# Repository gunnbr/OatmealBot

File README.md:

# OatmealBot
OatmealBot is a robot built on a circular platform using 3 [omni wheels](https://en.wikipedia.org/wiki/Omni_wheel) and
controlled using a PS3 controller. It's named OatmealBot because it was
originally designed so the control hardware could be hidden under a
cylindrical box of oatmeal.

## Features
This OatmealBot controller is built on top of the
[Adafruit Motor Hat](http://adafru.it/2348). This board provides the
following features on top of that:
* Powers the Hat and the Pi from a [Pololu 5V regulator](https://www.pololu.com/product/2858)
* Plug for 4
[Pololu motors with quadrature encoder](https://www.pololu.com/product/3240)
* Plugs for 3 servos
* 2 high power outputs
* Plug for [SPI OLED display](http://adafru.ti/938)
* 2 LED (status & error)
* Plug for
[FTDI TTL serial to USB adapter](http://www.ftdichip.com/Support/Documents/DataSheets/Cables/DS_TTL-232R_CABLES.pdf)

## History
This was initially envisioned using a SAMD21 controller so the motor
encoders could be read by hardware counters. However, I couldn't find
a good Bluetooth driver that worked. Although I found some existing
drivers that could be ported, I realized I could just as well get
a Raspberry Pi Zero W with built-in Bluetooth and a motor hat and
see how well it works without reading the encoders. Turns out it
worked fairly well, so I kept working down this path.

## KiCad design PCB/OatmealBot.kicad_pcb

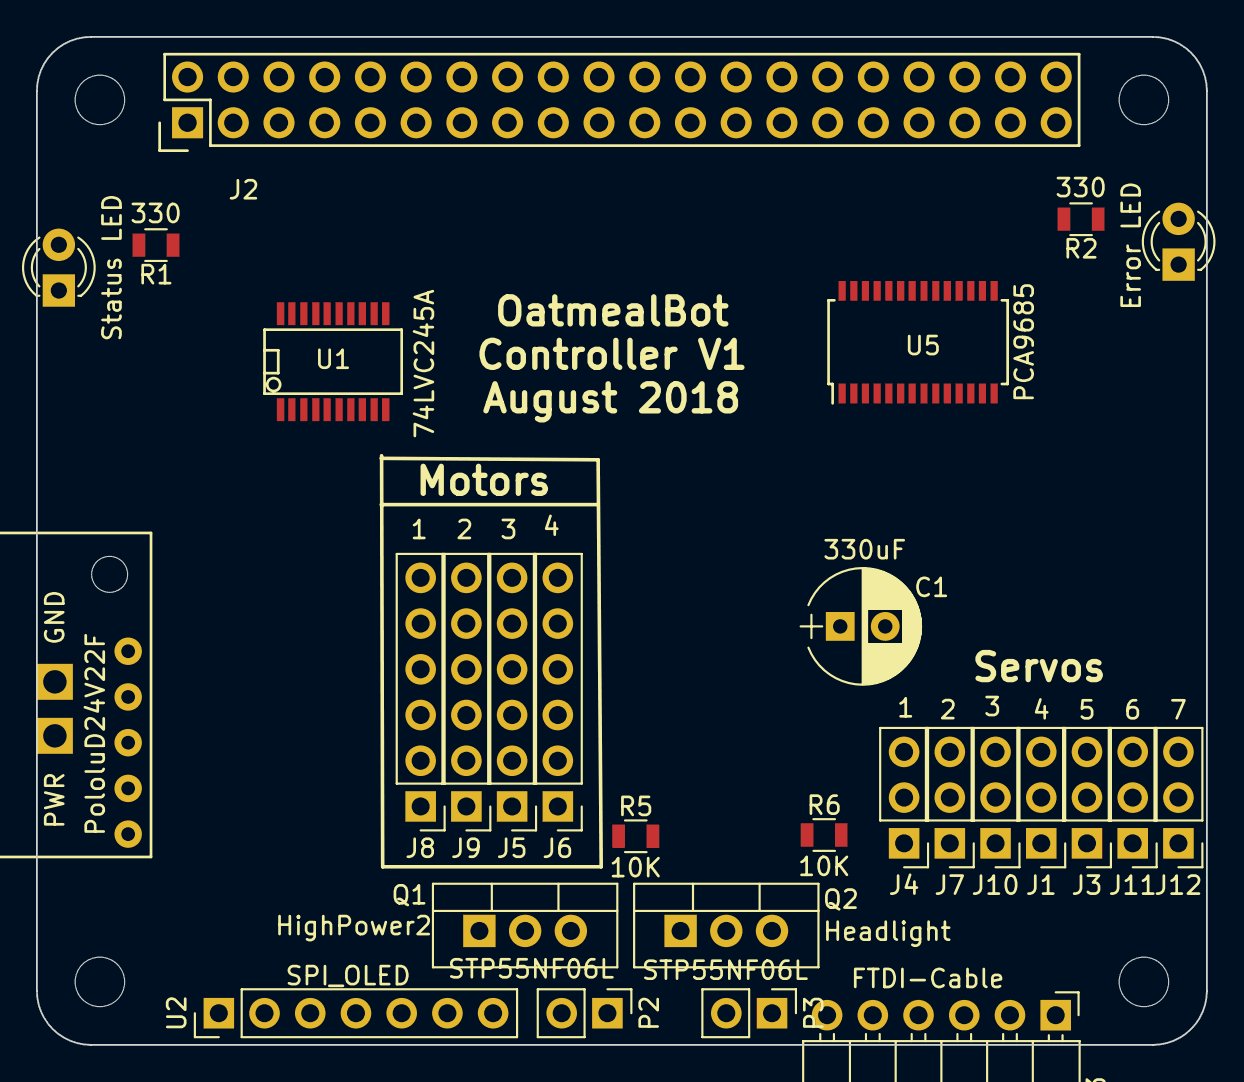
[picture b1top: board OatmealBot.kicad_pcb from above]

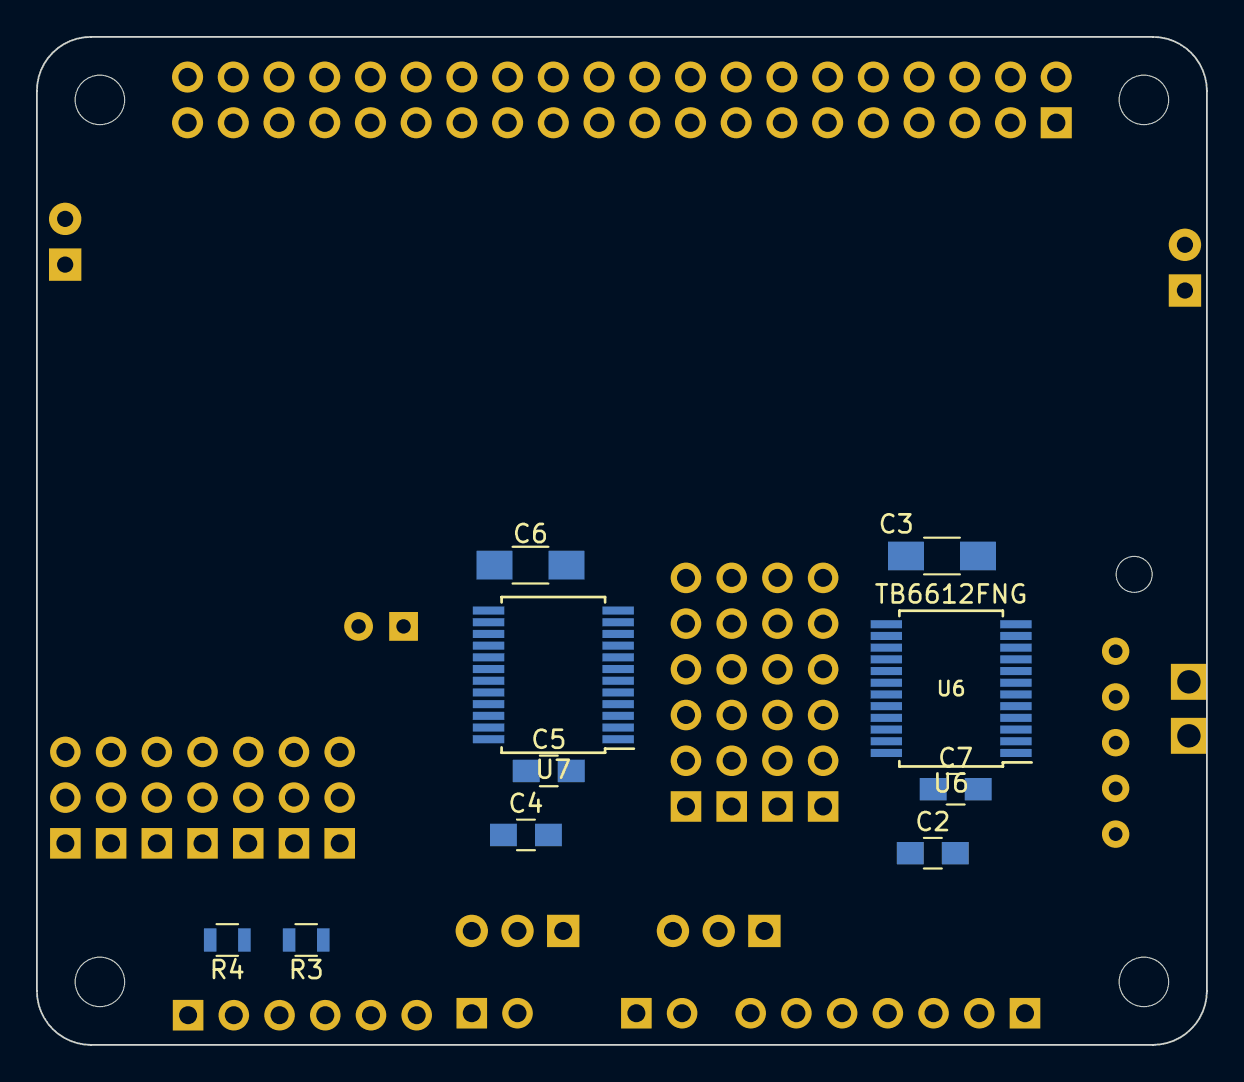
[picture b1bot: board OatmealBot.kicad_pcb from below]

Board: 2 copper layers, 65.0 x 56.0 mm, 39 parts (10 on the bottom side), 65 nets, no tracks yet.

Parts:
C1: 330uF; CP_Radial_D6.3mm_P2.50mm
C2, C4: 10uF; C_0805_HandSoldering
C3, C6: 47uF; C_1206_HandSoldering
C5, C7: 0.1uF; C_0805_HandSoldering
D1: Status LED; LED_D3.0mm
D2: Error LED; LED_D3.0mm
J1: 4; Pin_Header_Straight_1x03_Pitch2.54mm
J2: RPi_GPIO; Pin_Header_Straight_2x20
J3: 5; Pin_Header_Straight_1x03_Pitch2.54mm
J4: 1; Pin_Header_Straight_1x03_Pitch2.54mm
J5: 3; Pin_Header_Straight_1x06_Pitch2.54mm
J6: 4; Pin_Header_Straight_1x06_Pitch2.54mm
J7: 2; Pin_Header_Straight_1x03_Pitch2.54mm
J8: 1; Pin_Header_Straight_1x06_Pitch2.54mm
J9: 2; Pin_Header_Straight_1x06_Pitch2.54mm
J10: 3; Pin_Header_Straight_1x03_Pitch2.54mm
J11: 6; Pin_Header_Straight_1x03_Pitch2.54mm
J12: 7; Pin_Header_Straight_1x03_Pitch2.54mm
P1: Motor Hat Power; Power_Connector_Soldered
P2: HighPower2; Pin_Header_Straight_1x02_Pitch2.54mm
P3: Headlight; Pin_Header_Straight_1x02_Pitch2.54mm
Q1, Q2: STP55NF06L; TO-220-3_Vertical
R1, R2: 330; R_0805
R3, R4: R; R_0805
R5, R6: 10K; R_0805
U1: 74LVC245A; SSOP-20
U2: SPI_OLED; Socket_Strip_Straight_1x07_Pitch2.54mm
U3: FTDI-Cable; Pin_Header_Angled_1x06_Pitch2.54mm
U4: PololuD24V22F
U5: PCA9685; TSSOP-28_4.4x9.7mm_Pitch0.65mm
U6, U7: TB6612FNG; SSOP-24_5.3x8.2mm_Pitch0.65mm

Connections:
+3V3: C2.1, C4.1, C5.1, C7.1, J2.1, J2.17, U1.1, U1.20, U2.2, U5.24, U5.28, U6.19, U6.20, U7.19, U7.20
+5V: C1.1, J1.2, J2.2, J2.4, J3.2, J4.2, J5.4, J6.4, J7.2, J8.4, J9.4, J10.2, J11.2, J12.2, U4.5
+12V: C3.1, C6.1, P1.2, U4.3, U6.13, U6.14, U6.24, U7.13, U7.14, U7.24
/MotorController/Motor1+: J8.1, U6.1, U6.2
/MotorController/Motor1-: J8.2, U6.5, U6.6
/MotorController/Motor2+: J9.1, U6.7, U6.8
/MotorController/Motor2-: J9.2, U6.11, U6.12
/MotorController/Motor3+: J5.1, U7.1, U7.2
/MotorController/Motor3-: J5.2, U7.5, U7.6
/MotorController/Motor4+: J6.1, U7.7, U7.8
/MotorController/Motor4-: J6.2, U7.11, U7.12
ENC1A: J2.40, U1.17
ENC1B: J2.38, U1.18
ENC2A: J2.36, U1.15
ENC2B: J2.37, U1.16
ENC3A: J2.33, U1.13
ENC3B: J2.35, U1.14
ENC4A: J2.31, U1.11
ENC4B: J2.29, U1.12
GND: C1.2, C2.2, C3.2, C4.2, C5.2, C6.2, C7.2, D1.1, D2.1, J1.1, J2.6, J2.9, J2.14, J2.20, J2.25, J2.30, J2.34, J2.39, J3.1, J4.1, J5.3, J6.3, J7.1, J8.3, J9.3, J10.1, J11.1, J12.1, P1.1, P2.1, P3.1, Q1.3, Q2.3, R4.2, R5.2, R6.2, U1.10, U1.19, U2.1, U3.1, U4.4, U5.1, U5.2, U5.3, U5.4, U5.5, U5.14, U5.23, U5.25, U6.3, U6.4, U6.9, U6.10, U6.18, U7.3, U7.4, U7.9, U7.10, U7.18
Headlight: J2.7, Q2.1, R6.1
HighPower2: J2.13, Q1.1, R5.1
MOSI: J2.19, U2.4
unnamed: D1.2, R1.2
unnamed: D2.2, R2.1
unnamed: J2.15, R1.1
unnamed: J2.16, R2.2
unnamed: J5.5, U1.7
unnamed: J5.6, U1.6
unnamed: J6.5, U1.9
unnamed: J6.6, U1.8
unnamed: J8.5, U1.3
unnamed: J8.6, U1.2
unnamed: J9.5, U1.5
unnamed: J9.6, U1.4
unnamed: P2.2, Q1.2
unnamed: P3.2, Q2.2
unnamed: R3.1, U3.4
unnamed: U5.8, U6.23
unnamed: U5.9, U6.22
unnamed: U5.10, U6.21
unnamed: U5.11, U6.17
unnamed: U5.12, U6.16
unnamed: U5.13, U6.15
unnamed: U5.15, U7.23
unnamed: U5.16, U7.22
unnamed: U5.17, U7.21
unnamed: U5.18, U7.17
unnamed: U5.19, U7.16
unnamed: U5.20, U7.15
OLED_CS: J2.24, U2.7
OLED_DC: J2.22, U2.6
OLED_RESET: J2.18, U2.5
PI_RXD: J2.10, R3.2, R4.1
PI_TXD: J2.8, U3.5
SCL: J2.5, U5.26
SCLK: J2.23, U2.3
SDA: J2.3, U5.27
Servo1: J2.32, J4.3
Servo2: J2.12, J7.3
Servo3: J2.11, J10.3
Servo4: J1.3, U5.6
Servo5: J3.3, U5.7
Servo6: J11.3, U5.21
Servo7: J12.3, U5.22

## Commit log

2018-05-31 Initial re-implementation of oatmealbot using pigpio instead of relying on pygame. Added status indicator LED. Doesn't actually control the motors.
2018-05-31 Scale the values from the joysticks to the values expected by TranslateMotorInputs.
2018-05-31 Added support for driving the motors. Now works better than the old pygame version since it is able to start at boot! (And also provides the status LED.)
2018-06-13 Added README and reorganized a little.
2018-06-13 Added docs, mechanical design, and PCB design.
2018-06-13 Add license
2018-06-16 Added GPIO docs that should have been added in the last commit.
2018-06-16 Added 5V to 3.3V level shifter on the encoder outputs. Hooked up all encoder outputs.
2018-06-16 Added LEDs and servo connectors
2018-06-19 Added power connectors
2018-06-20 Added serial port connector
2018-06-20 Added OLED SPI connector
2018-06-22 Hooked up the servo outputs correctly. Fixed a lot of design rule problems.
2018-06-22 Started assigning some footprints. Initial PCB layout.
2018-06-30 Added MOSFET for headlight
2018-07-01 Added second high power connector
2018-07-04 Updated README with more details about exactly what the board does.
2018-07-04 Fixed spelling of OatmealBot (facepalm) and added link for omni wheel.
2018-07-04 Fixed PCB edges to connect properly. Removed extra explanation text about selecting the right footprint. Attempted to fix 3D models, but it hasn't worked right.
2018-07-05 Fixed some of the 3D models. SPI_OLED and the Pololu power connector still aren't lined up properly though.
2018-07-05 Fixed placement of 3D model for Pololu power and SPI_OLED.
2018-07-05 Updated to KiCad 4.0.7 (which lost the 3D models I had just gotten working) Assigned more footprints.
2018-07-06 Created proper footprint for the voltage regulator so it's easier to see how much space it takes up on the board. Changed the board layout to fit the regulator. Fixed some more 3D files
2018-07-13 Added 4 more servo headers for the extra PWM outputs. Rearranged the schematic a little to fix in US letter size paper.
2018-07-14 Fixed servos, added PWM chip
2018-07-17 Created symbol for TB6612FNG motor driver. Added first motor driver and hooked it up.
2018-07-18 Added second motor driver. Got everything hooked up back.
2018-07-18 Connected I2C, fixed ERC errors
    Connected I2C to the PWM controller.
    Fixed ERC errors.
2018-07-19 Added caps for the motor drivers
2018-07-22 Cleaned up, renamed a few things and added all footprints.
2018-07-22 Fixed the name of the motor controller sheet.
2018-07-22 Started work on the board layout.
2018-07-24 Initial lay out of servo headers and all components.
2018-07-25 Footprint changes and board layout changes
2018-08-01 PCB layout changes
    Move things around to make the high power tracks shorter
2018-08-05 Layout refinement, better power connector
